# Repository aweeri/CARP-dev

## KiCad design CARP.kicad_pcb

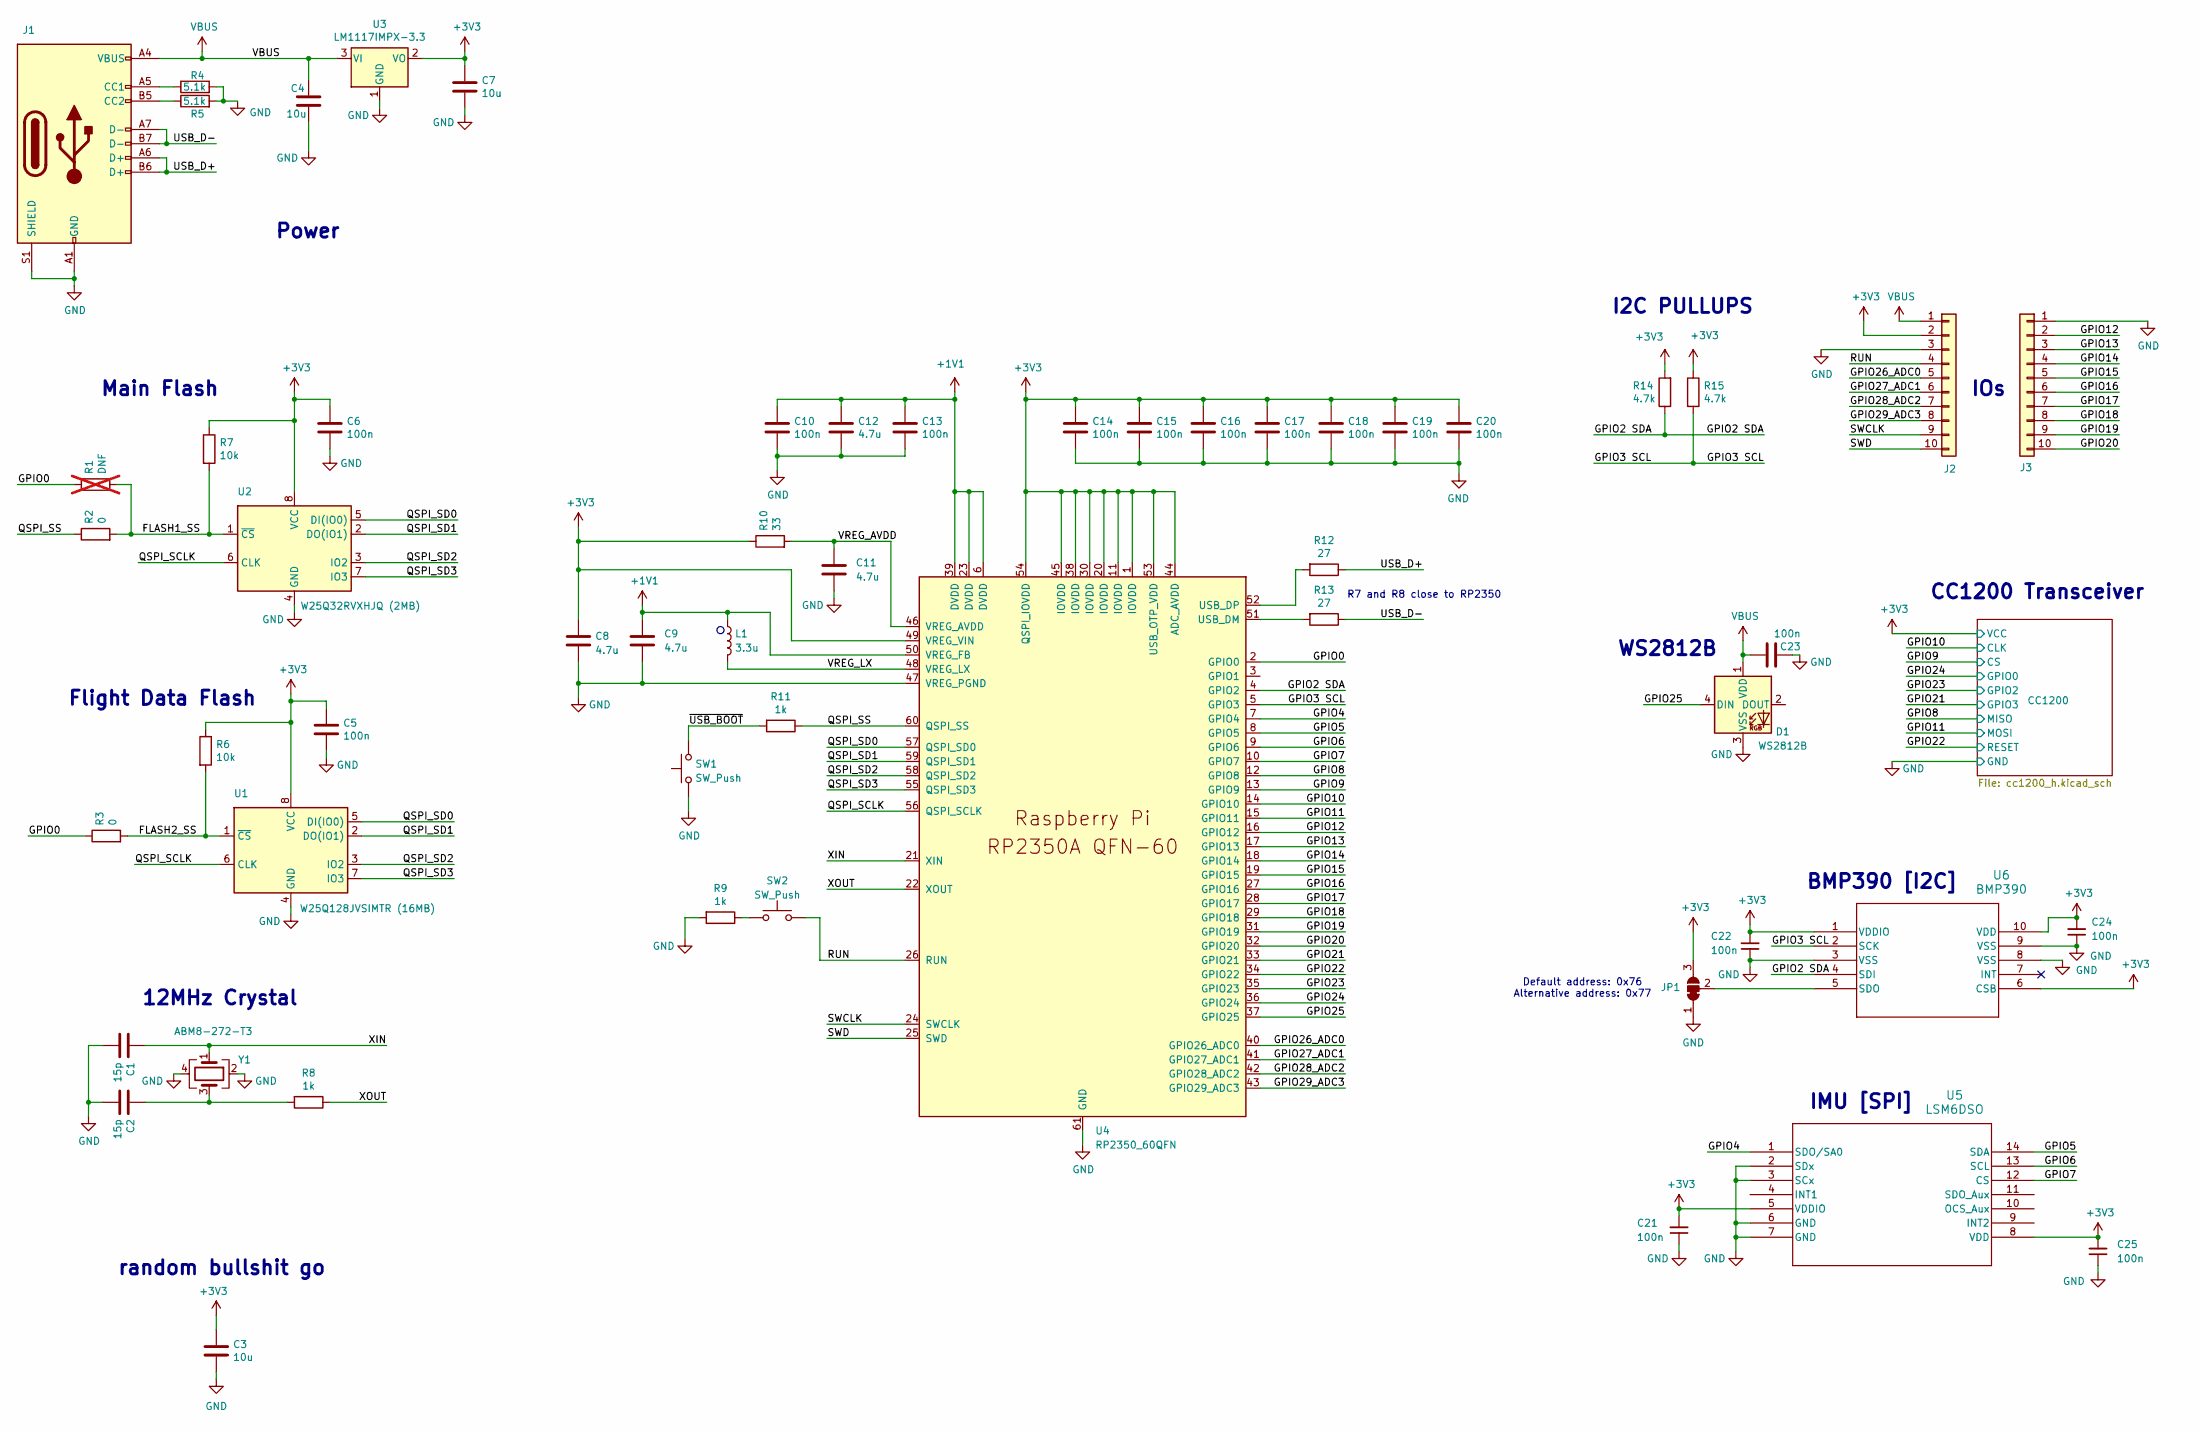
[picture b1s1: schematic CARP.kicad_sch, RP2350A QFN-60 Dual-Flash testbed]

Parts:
C1, C2: 15p; C_0402_1005Metric
C3, C4, C7: 10u; C_0805_2012Metric
C5, C6, C10, C13, C14, C15, C16, C17, C18, C19, C20, C21, C22, C24, C25: 100n; C_0402_1005Metric
C8, C9: 4.7u; C_0402_1005Metric_small_pads
C11, C12: 4.7u; C_0402_1005Metric
C23: 100n; C_0603_1608Metric
D1: WS2812B; LED_WS2812B_PLCC4_5.0x5.0mm_P3.2mm
J1: USB_C_Receptacle_USB2.0_14P; USB_C_Receptacle_GCT_USB4105-xx-A_16P_TopMnt_Horizontal
J2, J3: Conn_01x10; PinHeader_1x10_P2.54mm_Vertical
JP1: SolderJumper_3_Bridged12; SolderJumper-3_P1.3mm_Bridged12_RoundedPad1.0x1.5mm_NumberL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
L1: 3.3u; L_pol_2016
R1: DNF; R_0603_1608Metric; not fitted
R2, R3: 0; R_0603_1608Metric
R4, R5: 5.1k; R_0402_1005Metric
R6, R7: 10k; R_0603_1608Metric
R8: 1k; R_0402_1005Metric
R9, R11: 1k; R_0603_1608Metric
R10: 33; R_0402_1005Metric
R12, R13: 27; R_0402_1005Metric
R14, R15: 4.7k; R_0402_1005Metric
SW1, SW2: SW_Push; SW_Push_1P1T_NO_Vertical_Wuerth_434133025816
U1: W25Q128JVSIMTR (16MB); SOIC-8_5.3x5.3mm_P1.27mm
U2: W25Q32RVXHJQ (2MB); SOIC-8_5.3x5.3mm_P1.27mm
U3: LM1117IMPX-3.3; SOT-223-3_TabPin2
U4: RP2350_60QFN; RP2350-QFN-60-1EP_7x7_P0.4mm_EP3.4x3.4mm_ThermalVias
U5: LSM6DSO; LGA-14L_2P5X3X0P86_STM
U6: BMP390; 10LGA_2X2X0p75_BOS
Y1: ABM8-272-T3; Crystal_SMD_3225-4Pin_3.2x2.5mm

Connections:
+1V1: C9.1, C10.1, C12.1, C13.1, L1.1, U4.6 (DVDD), U4.23 (DVDD), U4.39 (DVDD), U4.50 (VREG_FB)
+3V3: C3.1, C5.1, C6.1, C7.1, C8.1, C14.1, C15.1, C16.1, C17.1, C18.1, C19.1, C20.1, C21.2, C22.2, C24.2, C25.2, J2.2, JP1.3 (B), R6.1, R7.1, R10.1, R14.2, R15.1, U1.8 (VCC), U2.8 (VCC), U3.2 (VO), U4.1 (IOVDD), U4.11 (IOVDD), U4.20 (IOVDD), U4.30 (IOVDD), U4.38 (IOVDD), U4.44 (ADC_AVDD), U4.45 (IOVDD), U4.49 (VREG_VIN), U4.53 (USB_OTP_VDD), U4.54 (QSPI_IOVDD), U5.5 (VDDIO), U5.8 (VDD), U6.1 (VDDIO), U6.6 (CSB), U6.10 (VDD); also elsewhere on the board
/FLASH1_SS: R1.2, R2.2, R7.2, U2.1 (~CS)
/FLASH2_SS: R3.2, R6.2, U1.1 (~CS)
/GPIO0: R1.1, R3.1, U4.2 (GPIO0)
/GPIO2 SDA: R14.1, U4.4 (GPIO2), U6.4 (SDI)
/GPIO3 SCL: R15.2, U4.5 (GPIO3), U6.2 (SCK)
/GPIO4: U4.7 (GPIO4), U5.1 (SDO/SA0)
/GPIO5: U4.8 (GPIO5), U5.14 (SDA)
/GPIO6: U4.9 (GPIO6), U5.13 (SCL)
/GPIO7: U4.10 (GPIO7), U5.12 (CS)
/GPIO8: U4.12 (GPIO8); also elsewhere on the board
/GPIO9: U4.13 (GPIO9); also elsewhere on the board
/GPIO10: U4.14 (GPIO10); also elsewhere on the board
/GPIO11: U4.15 (GPIO11); also elsewhere on the board
/GPIO12: J3.2, U4.16 (GPIO12)
/GPIO13: J3.3, U4.17 (GPIO13)
/GPIO14: J3.4, U4.18 (GPIO14)
/GPIO15: J3.5, U4.19 (GPIO15)
/GPIO16: J3.6, U4.27 (GPIO16)
/GPIO17: J3.7, U4.28 (GPIO17)
/GPIO18: J3.8, U4.29 (GPIO18)
/GPIO19: J3.9, U4.31 (GPIO19)
/GPIO20: J3.10, U4.32 (GPIO20)
/GPIO21: U4.33 (GPIO21); also elsewhere on the board
/GPIO22: U4.34 (GPIO22); also elsewhere on the board
/GPIO23: U4.35 (GPIO23); also elsewhere on the board
/GPIO24: U4.36 (GPIO24); also elsewhere on the board
/GPIO25: D1.4 (DIN), U4.37 (GPIO25)
/GPIO26_ADC0: J2.5, U4.40 (GPIO26_ADC0)
/GPIO27_ADC1: J2.6, U4.41 (GPIO27_ADC1)
/GPIO28_ADC2: J2.7, U4.42 (GPIO28_ADC2)
/GPIO29_ADC3: J2.8, U4.43 (GPIO29_ADC3)
/QSPI_SCLK: U1.6 (CLK), U2.6 (CLK), U4.56 (QSPI_SCLK)
/QSPI_SD0: U1.5 (DI(IO0)), U2.5 (DI(IO0)), U4.57 (QSPI_SD0)
/QSPI_SD1: U1.2 (DO(IO1)), U2.2 (DO(IO1)), U4.59 (QSPI_SD1)
/QSPI_SD2: U1.3 (IO2), U2.3 (IO2), U4.58 (QSPI_SD2)
/QSPI_SD3: U1.7 (IO3), U2.7 (IO3), U4.55 (QSPI_SD3)
/QSPI_SS: R2.1, R11.1, U4.60 (QSPI_SS)
/RUN: J2.4, SW2.2, U4.26 (RUN)
/SWCLK: J2.9, U4.24 (SWCLK)
/SWD: J2.10, U4.25 (SWD)
/USB_D+: J1.A6 (D+), J1.B6 (D+), R12.1
/USB_D-: J1.A7 (D-), J1.B7 (D-), R13.1
/VREG_AVDD: C11.1, R10.2, U4.46 (VREG_AVDD)
/VREG_LX: L1.2, U4.48 (VREG_LX)
/XIN: C1.1, U4.21 (XIN), Y1.1
/XOUT: R8.1, U4.22 (XOUT)
/~USB_BOOT: R11.2, SW1.2
GND: C1.2, C2.2, C3.2, C4.2, C5.2, C6.2, C7.2, C8.2, C9.2, C10.2, C11.2, C12.2, C13.2, C14.2, C15.2, C16.2, C17.2, C18.2, C19.2, C20.2, C21.1, C22.1, C23.2, C24.1, C25.1, D1.3 (VSS), J1.A1 (GND), J1.A12 (GND), J1.B1 (GND), J1.B12 (GND), J1.S1 (SHIELD), J2.3, J3.1, JP1.1 (A), R4.2, R5.2, R9.2, SW1.1, U1.4 (GND), U2.4 (GND), U3.1 (GND), U4.47 (VREG_PGND), U4.61 (GND), U5.2 (SDx), U5.3 (SCx), U5.6 (GND), U5.7 (GND), U6.3 (VSS), U6.8 (VSS), U6.9 (VSS), Y1.2, Y1.4; also elsewhere on the board
unnamed: C2.1, R8.2, Y1.3
unnamed: J1.A5 (CC1), R4.1
unnamed: J1.B5 (CC2), R5.1
unnamed: JP1.2 (C), U6.5 (SDO)
unnamed: R9.1, SW2.1
unnamed: R13.2, U4.51 (USB_DM)
unnamed: R12.2, U4.52 (USB_DP)
VBUS: C4.1, C23.1, D1.1 (VDD), J1.A4 (VBUS), J1.A9 (VBUS), J1.B4 (VBUS), J1.B9 (VBUS), J2.1, U3.3 (VI)

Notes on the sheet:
random bullshit go
IOs
I2C PULLUPS
CC1200 Transceiver
Main Flash
WS2812B
R7 and R8 close to RP2350
IMU [SPI]
Default address: 0x76 Alternative address: 0x77
BMP390 [I2C]
Flight Data Flash
12MHz Crystal
Power

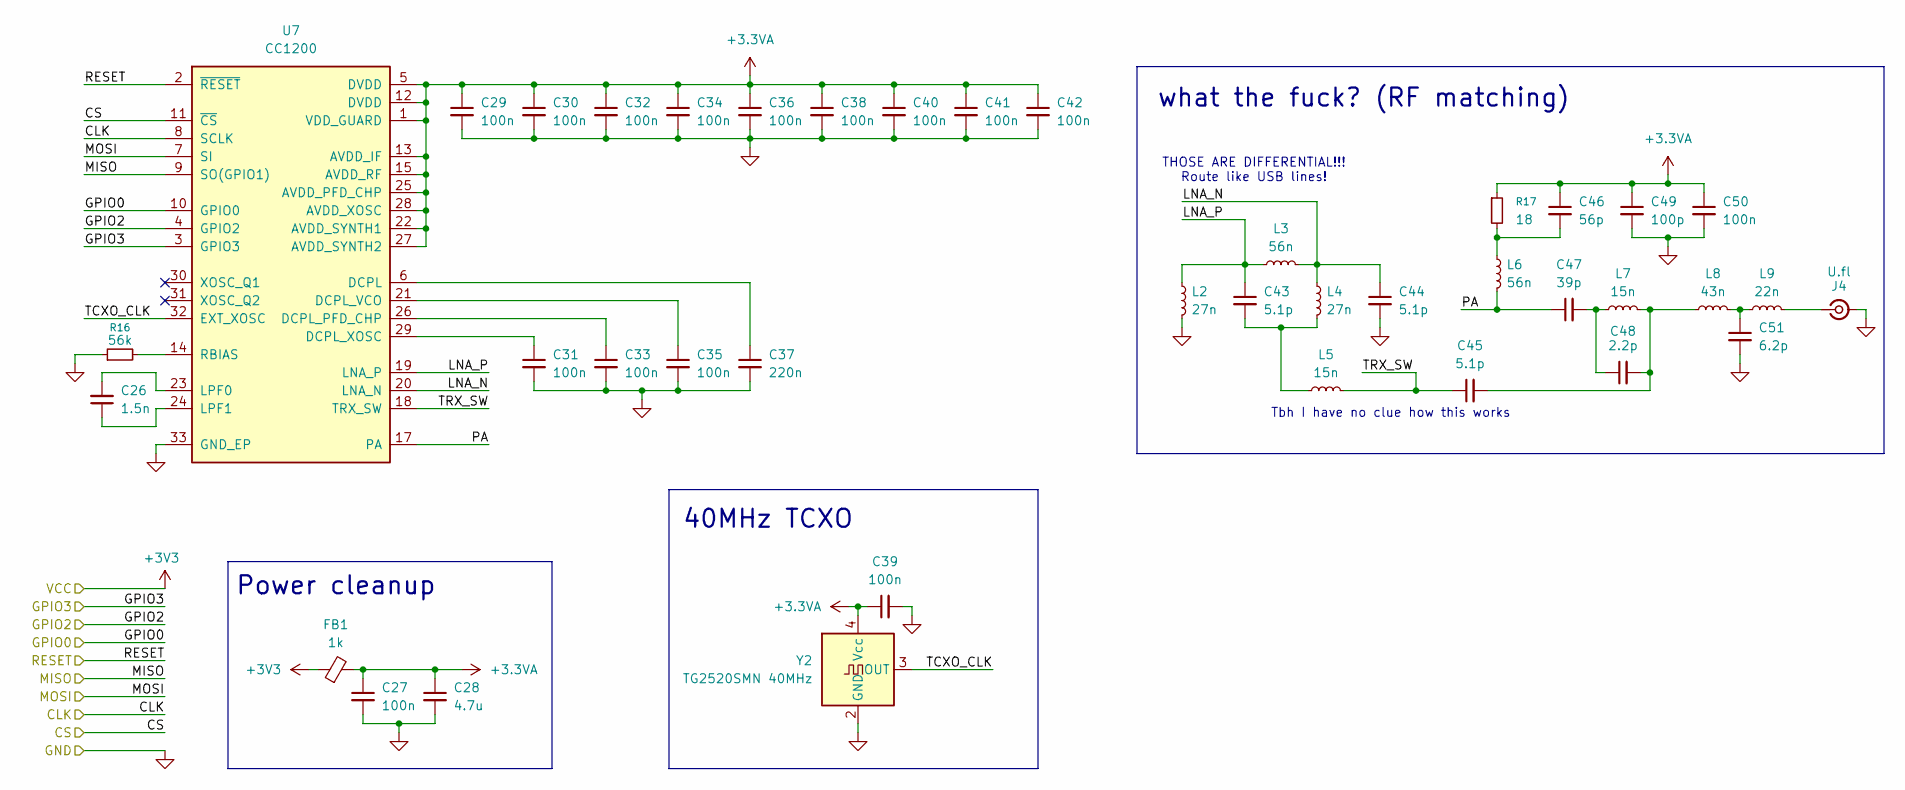
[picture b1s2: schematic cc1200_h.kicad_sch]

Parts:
C26: 1.5n; C_0402_1005Metric
C27, C29, C30, C31, C32, C33, C34, C35, C36, C38, C39, C40, C41, C42, C50: 100n; C_0402_1005Metric
C28: 4.7u; C_0805_2012Metric
C37: 220n; C_0402_1005Metric
C43, C44, C45: 5.1p; C_0402_1005Metric
C46: 56p; C_0402_1005Metric
C47: 39p; C_0402_1005Metric
C48: 2.2p; C_0402_1005Metric
C49: 100p; C_0402_1005Metric
C51: 6.2p; C_0402_1005Metric
FB1: 1k; L_0402_1005Metric
J4: U.fl; U.FL_Hirose_U.FL-R-SMT-1_Vertical
L2, L4: 27n; L_0402_1005Metric
L3, L6: 56n; L_0402_1005Metric
L5, L7: 15n; L_0402_1005Metric
L8: 43n; L_0402_1005Metric
L9: 22n; L_0402_1005Metric
R16: 56k; R_0402_1005Metric
R17: 18; R_0402_1005Metric
U7: CC1200; QFN-32-1EP_5x5mm_P0.5mm_EP3.45x3.45mm
Y2: TG2520SMN 40MHz; Oscillator_SMD_SeikoEpson_TG2520SMN-xxx-xxxxxx-4Pin_2.5x2.0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

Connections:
+3.3VA: C27.1, C28.1, C29.1, C30.1, C32.1, C34.1, C36.1, C38.1, C39.1, C40.1, C41.1, C42.1, C46.1, C49.1, C50.1, FB1.2, R17.1, U7.1 (VDD_GUARD), U7.5 (DVDD), U7.12 (DVDD), U7.13 (AVDD_IF), U7.15 (AVDD_RF), U7.22 (AVDD_SYNTH1), U7.25 (AVDD_PFD_CHP), U7.27 (AVDD_SYNTH2), U7.28 (AVDD_XOSC), Y2.4 (Vcc)
+3V3: FB1.1; also elsewhere on the board
/CC1200/LNA_N: C44.1, L3.2, L4.1, U7.20 (LNA_N)
/CC1200/LNA_P: C43.1, L2.1, L3.1, U7.19 (LNA_P)
/CC1200/PA: C47.1, L6.2, U7.17 (PA)
/CC1200/TCXO_CLK: U7.32 (EXT_XOSC), Y2.3 (OUT)
/CC1200/TRX_SW: C45.1, L5.2, U7.18 (TRX_SW)
/GPIO8: U7.9 (SO(GPIO1)); also elsewhere on the board
/GPIO9: U7.11 (~CS); also elsewhere on the board
/GPIO10: U7.8 (SCLK); also elsewhere on the board
/GPIO11: U7.7 (SI); also elsewhere on the board
/GPIO21: U7.3 (GPIO3); also elsewhere on the board
/GPIO22: U7.2 (~RESET); also elsewhere on the board
/GPIO23: U7.4 (GPIO2); also elsewhere on the board
/GPIO24: U7.10 (GPIO0); also elsewhere on the board
GND: C27.2, C28.2, C29.2, C30.2, C31.2, C32.2, C33.2, C34.2, C35.2, C36.2, C37.2, C38.2, C39.2, C40.2, C41.2, C42.2, C44.2, C49.2, C50.2, C51.2, J4.2 (Ext), L2.2, R16.1, U7.33 (GND_EP), Y2.2 (GND); also elsewhere on the board
unnamed: C43.2, L4.2, L5.1
unnamed: C45.2, C48.2, L7.2, L8.1
unnamed: C46.2, L6.1, R17.2
unnamed: C47.2, C48.1, L7.1
unnamed: C51.1, L8.2, L9.1
unnamed: J4.1 (In), L9.2
unnamed: C37.1, U7.6 (DCPL)
unnamed: C33.1, U7.26 (DCPL_PFD_CHP)
unnamed: C35.1, U7.21 (DCPL_VCO)
unnamed: C31.1, U7.29 (DCPL_XOSC)
unnamed: C26.2, U7.23 (LPF0)
unnamed: C26.1, U7.24 (LPF1)
unnamed: R16.2, U7.14 (RBIAS)

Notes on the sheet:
40MHz TCXO
what the fuck? (RF matching)
Power cleanup
THOSE ARE DIFFERENTIAL!!! Route like USB lines!
Tbh I have no clue how this works

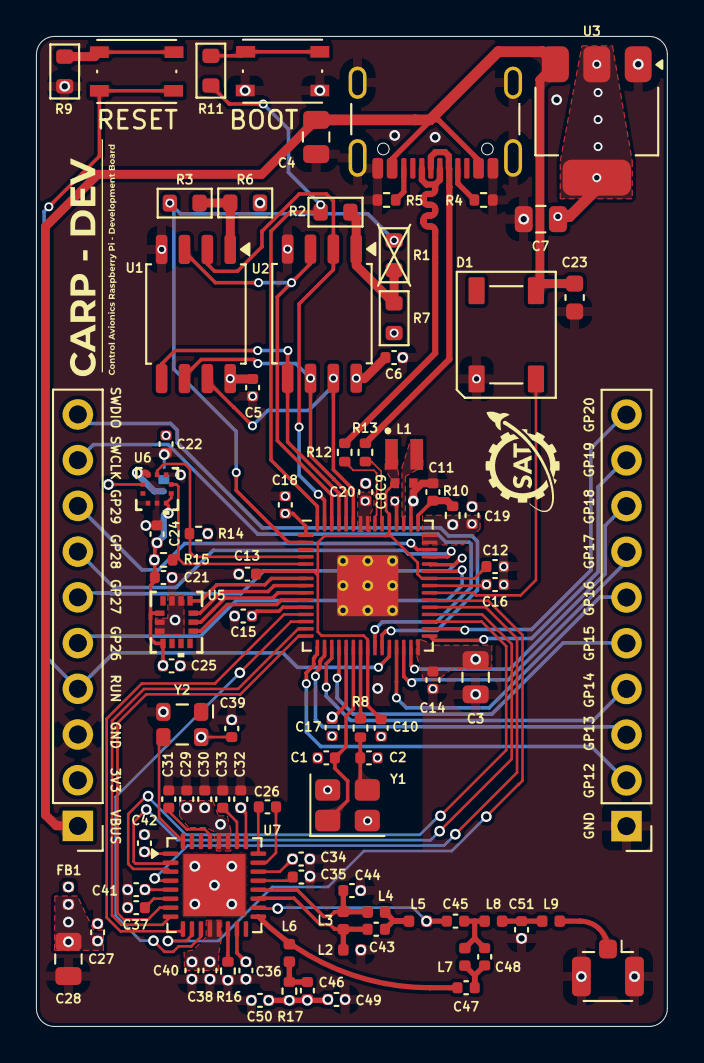
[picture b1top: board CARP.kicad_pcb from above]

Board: 4 copper layers, 35.0 x 55.0 mm, 95 parts (1 on the bottom side), 77 nets.

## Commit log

2026-03-22 add CARP-dev files
2026-03-22 Add gitignore and specify PCB stackup
2026-03-22 Preliminary CC1200 decoupling design
2026-03-22 halved silkscreen text size
2026-03-22 further work on the essential modules
2026-03-23 work
2026-03-23 stuff
2026-03-23 Add autosave files to .gitignore
2026-03-23 moar tracin
2026-03-23 Fix most DRC errors and preliminary CC1200 fit
2026-03-23 random bullshit go
2026-03-27 RF section complete, I think
2026-03-29 Finished PCB???
2026-03-29 QoL changes
2026-03-31 TRX_SW was crooked
2026-03-31 Also differential LNA lines
2026-03-31 silkscreen
